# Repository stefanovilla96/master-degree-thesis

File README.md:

# master-degree-thesis
Remote repository about master degree thesis in informatic engineering

# organization of the folders:
    - thesis : contains documentation about the project
    - Winter-v2_firmware : contains firmware for microcontroller for BIA measure with BIA Board & Winter v2
    - EDABoard : contains firmware for microcontroller for EDA Measure
    - EDA Board_Software : contains eclipse project for EDA measure

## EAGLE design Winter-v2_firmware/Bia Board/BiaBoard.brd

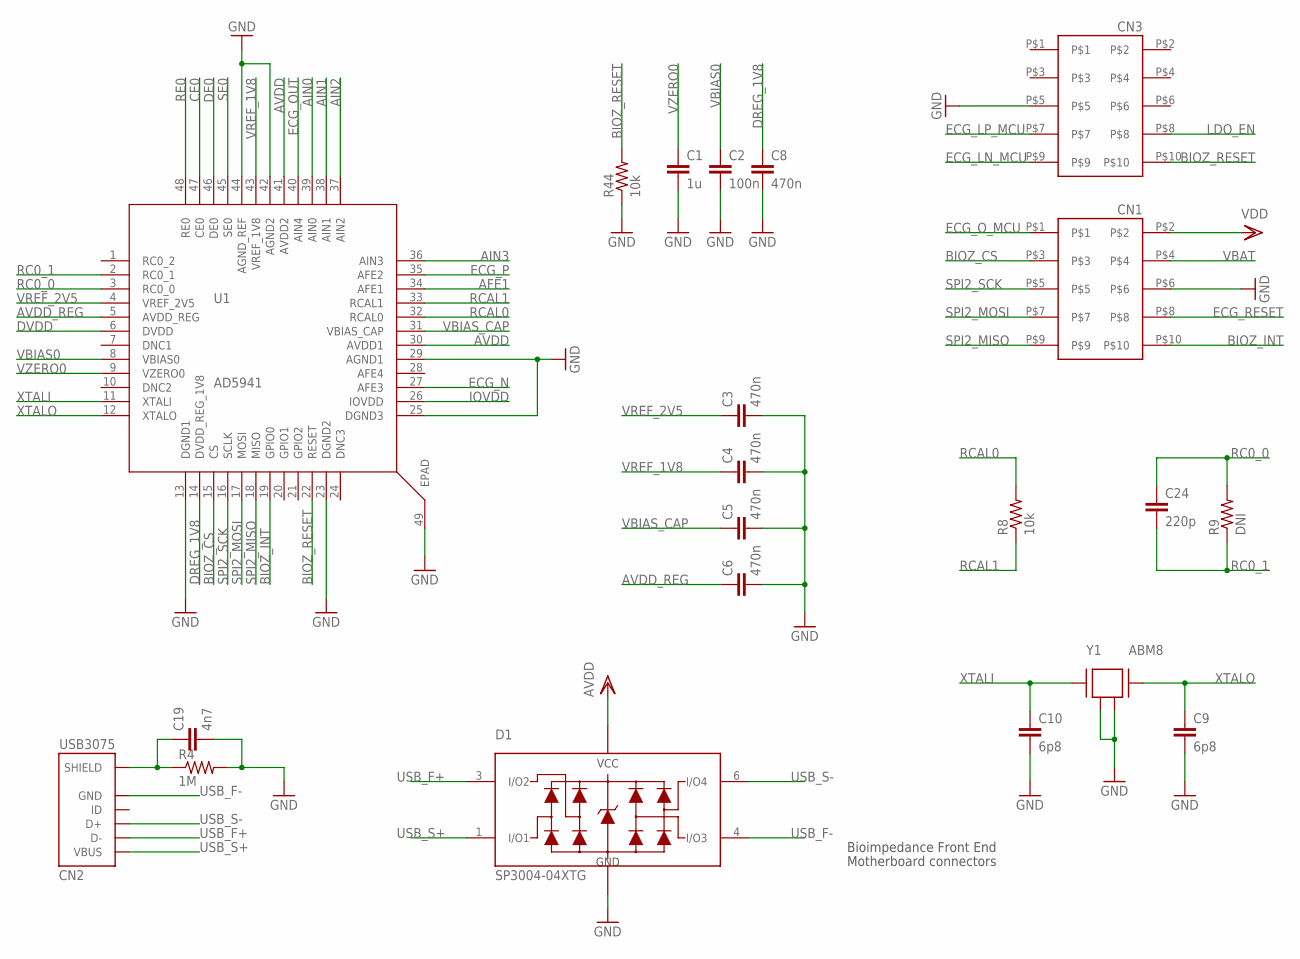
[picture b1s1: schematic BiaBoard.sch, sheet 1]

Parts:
C1: 1u; C0402
C2: 100n; C0402
C3, C4, C5, C6, C8: 470n; C0402
C9, C10: 6p8; C0402
C19: 4n7; C0402
C24: 220p; C0402
CN1, CN3: FTSH-105TO; FTSH-105-D
CN2: USB3075
D1: SP3004-04XTG; SOT50P160X60-6N
R4: 1M; 0402
R8: 10k; 0402; TOLERANCE 0.1%
R9: DNI; 0402
R44: 10k; 0402
U1: AD5941; QFN50P700X700X80-49T510N
Y1: ABM8

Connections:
AFE1: U1.34 (AFE1); also elsewhere on the board
AIN0: U1.39 (AIN0); also elsewhere on the board
AIN1: U1.38 (AIN1); also elsewhere on the board
AIN2: U1.37 (AIN2); also elsewhere on the board
AIN3: U1.36 (AIN3); also elsewhere on the board
AVDD: D1.5 (VCC), U1.30 (AVDD1), U1.41 (AVDD2); also elsewhere on the board
AVDD_REG: C6.P$1 (1), U1.5 (AVDD_REG)
BIOZ_CS: CN1.P$3, U1.15 (CS)
BIOZ_INT: CN1.P$10, U1.19 (GPIO0)
BIOZ_RESET: CN3.P$10, R44.P$2 (2), U1.22 (RESET)
CE0: U1.47 (CE0); also elsewhere on the board
DE0: U1.46 (DE0); also elsewhere on the board
DREG_1V8: C8.P$1 (1), U1.14 (DVDD_REG_1V8)
DVDD: U1.6 (DVDD); also elsewhere on the board
ECG_LN_MCU: CN3.P$9; also elsewhere on the board
ECG_LP_MCU: CN3.P$7; also elsewhere on the board
ECG_N: U1.27 (AFE3); also elsewhere on the board
ECG_OUT: U1.40 (AIN4); also elsewhere on the board
ECG_O_MCU: CN1.P$1; also elsewhere on the board
ECG_P: U1.35 (AFE2); also elsewhere on the board
ECG_RESET: CN1.P$8; also elsewhere on the board
GND: C1.P$2 (2), C2.P$2 (2), C3.P$2 (2), C4.P$2 (2), C5.P$2 (2), C6.P$2 (2), C8.P$2 (2), C9.P$2 (2), C10.P$2 (2), C19.P$2 (2), CN1.P$6, CN3.P$5, D1.2 (GND), R4.P$2 (2), R44.P$1 (1), U1.13 (DGND1), U1.23 (DGND2), U1.25 (DGND3), U1.29 (AGND1), U1.42 (AGND2), U1.44 (AGND_REF), U1.49 (EPAD), Y1.P$2 (2), Y1.P$4 (4); also elsewhere on the board
IOVDD: U1.26 (IOVDD); also elsewhere on the board
LDO_EN: CN3.P$8; also elsewhere on the board
unnamed: C19.P$1 (1), CN2.G1 (SHIELD), CN2.G2 (SHIELD), CN2.G3 (SHIELD), CN2.G4 (SHIELD), CN2.G5 (SHIELD), CN2.G6 (SHIELD), R4.P$1 (1)
RC0_0: C24.P$1 (1), R9.P$2 (2), U1.3 (RC0_0)
RC0_1: C24.P$2 (2), R9.P$1 (1), U1.2 (RC0_1)
RCAL0: R8.P$2 (2), U1.32 (RCAL0)
RCAL1: R8.P$1 (1), U1.33 (RCAL1)
RE0: U1.48 (RE0); also elsewhere on the board
SE0: U1.45 (SE0); also elsewhere on the board
SPI2_MISO: CN1.P$9, U1.18 (MISO)
SPI2_MOSI: CN1.P$7, U1.17 (MOSI)
SPI2_SCK: CN1.P$5, U1.16 (SCLK)
USB_F+: CN2.P2 (D-), D1.3 (I/O2); also elsewhere on the board
USB_F-: CN2.P5 (GND), D1.4 (I/O3); also elsewhere on the board
USB_S+: CN2.P1 (VBUS), D1.1 (I/O1); also elsewhere on the board
USB_S-: CN2.P3 (D+), D1.6 (I/O4); also elsewhere on the board
VBAT: CN1.P$4; also elsewhere on the board
VBIAS0: C2.P$1 (1), U1.8 (VBIAS0)
VBIAS_CAP: C5.P$1 (1), U1.31 (VBIAS_CAP)
VDD: CN1.P$2; also elsewhere on the board
VREF_1V8: C4.P$1 (1), U1.43 (VREF_1V8)
VREF_2V5: C3.P$1 (1), U1.4 (VREF_2V5)
VZERO0: C1.P$1 (1), U1.9 (VZERO0)
XTALI: C10.P$1 (1), U1.11 (XTALI), Y1.P$1 (1)
XTALO: C9.P$1 (1), U1.12 (XTALO), Y1.P$3 (3)

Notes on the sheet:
Bioimpedance Front End
Motherboard connectors

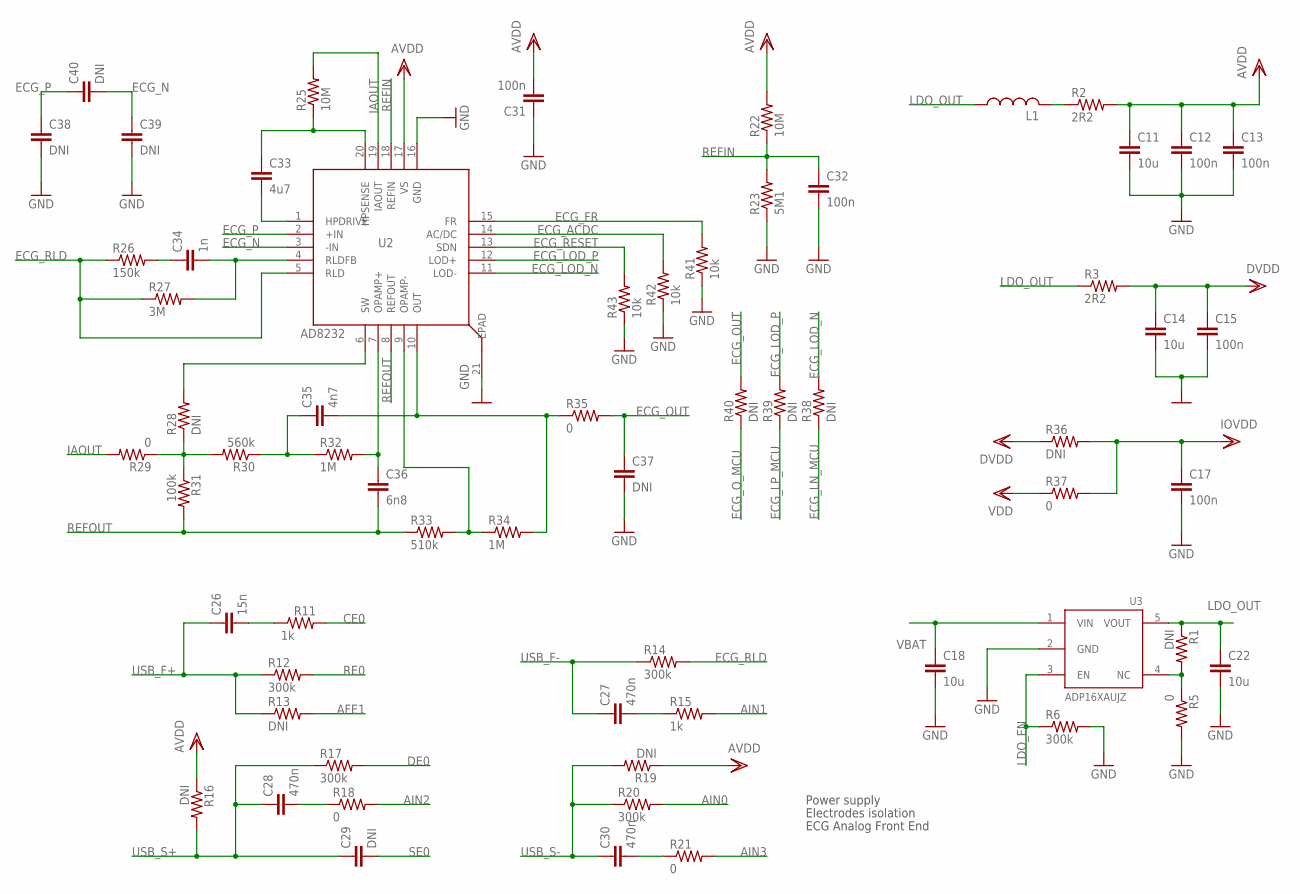
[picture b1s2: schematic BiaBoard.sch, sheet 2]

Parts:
C11, C14, C18, C22: 10u; C0603
C12, C13, C15, C17, C31, C32: 100n; C0402
C26: 15n; C0402
C27, C28, C30: 470n; C0402
C29, C38, C39, C40: DNI; C0402
C33: 4u7; C0402
C34: 1n; C0402
C35: 4n7; C0402
C36: 6n8; C0402
C37: DNI; C0603
L1: L0603; 0603
R1, R13, R16, R19, R28, R36, R38, R39, R40: DNI; 0402
R2, R3: 2R2; 0805
R5, R18, R21, R29, R35, R37: 0; 0402
R6, R12, R14, R17, R20: 300k; 0402
R11, R15: 1k; 0402
R22, R25: 10M; 0402
R23: 5M1; 0402
R26: 150k; 0402
R27: 3M; 0402
R30: 560k; 0402
R31: 100k; 0603
R32, R34: 1M; 0402
R33: 510k; 0402
R41, R42, R43: 10k; 0402
U2: AD8232; QFN50P400X400X75-21T260N
U3: ADP16XAUJZ; TSOT23-5L

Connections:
AFE1: R13.P$2 (2); also elsewhere on the board
AIN0: R20.P$2 (2); also elsewhere on the board
AIN1: R15.P$2 (2); also elsewhere on the board
AIN2: R18.P$2 (2); also elsewhere on the board
AIN3: R21.P$2 (2); also elsewhere on the board
AVDD: C11.P$1 (1), C12.P$1 (1), C13.P$1 (1), C31.P$2 (2), R2.P$2 (2), R16.P$1 (1), R19.P$1 (1), R22.P$2 (2), U2.17 (VS); also elsewhere on the board
CE0: R11.P$2 (2); also elsewhere on the board
DE0: R17.P$2 (2); also elsewhere on the board
DVDD: C14.P$1 (1), C15.P$1 (1), R3.P$2 (2), R36.P$1 (1); also elsewhere on the board
ECG_ACDC: R42.P$2 (2), U2.14 (AC/DC)
ECG_FR: R41.P$2 (2), U2.15 (FR)
ECG_LN_MCU: R38.P$1 (1); also elsewhere on the board
ECG_LOD_N: R38.P$2 (2), U2.11 (LOD-)
ECG_LOD_P: R39.P$2 (2), U2.12 (LOD+)
ECG_LP_MCU: R39.P$1 (1); also elsewhere on the board
ECG_N: C39.P$1 (1), C40.P$2 (2), U2.3 (-IN); also elsewhere on the board
ECG_OUT: C37.P$1 (1), R35.P$2 (2), R40.P$2 (2); also elsewhere on the board
ECG_O_MCU: R40.P$1 (1); also elsewhere on the board
ECG_P: C38.P$1 (1), C40.P$1 (1), U2.2 (+IN); also elsewhere on the board
ECG_RESET: R43.P$2 (2), U2.13 (SDN); also elsewhere on the board
ECG_RLD: R14.P$2 (2), R26.P$1 (1), R27.P$1 (1), U2.5 (RLD)
GND: C11.P$2 (2), C12.P$2 (2), C13.P$2 (2), C14.P$2 (2), C15.P$2 (2), C17.P$2 (2), C18.P$2 (2), C22.P$2 (2), C31.P$1 (1), C32.P$2 (2), C37.P$2 (2), C38.P$2 (2), C39.P$2 (2), R5.P$2 (2), R6.P$2 (2), R23.P$1 (1), R41.P$1 (1), R42.P$1 (1), R43.P$1 (1), U2.16 (GND), U2.21 (EPAD), U3.2 (GND); also elsewhere on the board
IAOUT: R25.P$2 (2), R29.P$2 (2), U2.19 (IAOUT)
IOVDD: C17.P$1 (1), R36.P$2 (2), R37.P$2 (2); also elsewhere on the board
LDO_EN: R6.P$1 (1), U3.3 (EN); also elsewhere on the board
LDO_OUT: C22.P$1 (1), L1.P$1 (1), R1.P$1 (1), R3.P$1 (1), U3.5 (VOUT)
unnamed: L1.P$2 (2), R2.P$1 (1)
unnamed: C26.P$2 (2), R11.P$1 (1)
unnamed: R1.P$2 (2), R5.P$1 (1), U3.4 (NC)
unnamed: C27.P$2 (2), R15.P$1 (1)
unnamed: C30.P$2 (2), R21.P$1 (1)
unnamed: C28.P$2 (2), R18.P$1 (1)
unnamed: C33.P$1 (1), R25.P$1 (1), U2.20 (HPSENSE)
unnamed: C34.P$2 (2), R27.P$2 (2), U2.4 (RLDFB)
unnamed: C33.P$2 (2), U2.1 (HPDRIVE)
unnamed: R28.P$1 (1), R29.P$1 (1), R30.P$2 (2), R31.P$1 (1)
unnamed: C34.P$1 (1), R26.P$2 (2)
unnamed: R28.P$2 (2), U2.6 (SW)
unnamed: C35.P$1 (1), R30.P$1 (1), R32.P$1 (1)
unnamed: C35.P$2 (2), R34.P$2 (2), R35.P$1 (1), U2.10 (OUT)
unnamed: C36.P$1 (1), R32.P$2 (2), U2.7 (OPAMP+)
unnamed: R33.P$2 (2), R34.P$1 (1), U2.9 (OPAMP-)
RE0: R12.P$2 (2); also elsewhere on the board
REFIN: C32.P$1 (1), R22.P$1 (1), R23.P$2 (2), U2.18 (REFIN)
REFOUT: C36.P$2 (2), R31.P$2 (2), R33.P$1 (1), U2.8 (REFOUT)
SE0: C29.P$2 (2); also elsewhere on the board
USB_F+: C26.P$1 (1), R12.P$1 (1), R13.P$1 (1); also elsewhere on the board
USB_F-: C27.P$1 (1), R14.P$1 (1); also elsewhere on the board
USB_S+: C28.P$1 (1), C29.P$1 (1), R16.P$2 (2), R17.P$1 (1); also elsewhere on the board
USB_S-: C30.P$1 (1), R19.P$2 (2), R20.P$1 (1); also elsewhere on the board
VBAT: C18.P$1 (1), U3.1 (VIN); also elsewhere on the board
VDD: R37.P$1 (1); also elsewhere on the board

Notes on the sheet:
Power supply
ECG Analog Front End
Electrodes isolation

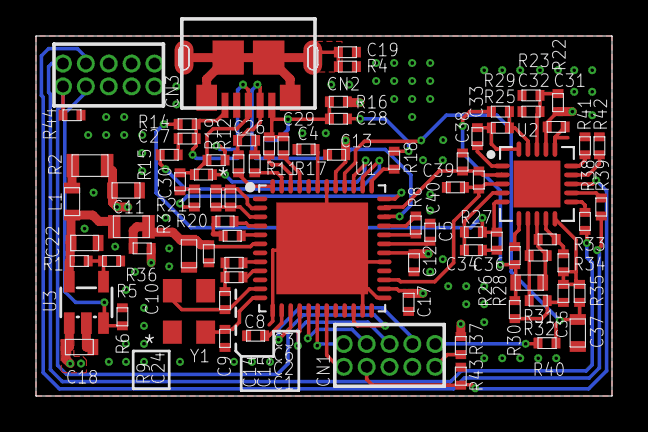
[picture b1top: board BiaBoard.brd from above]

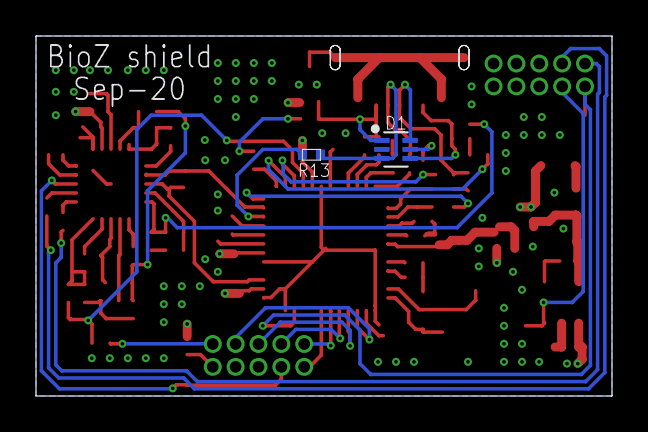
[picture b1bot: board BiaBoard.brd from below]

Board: 4 copper layers, 32.0 x 20.0 mm, 84 parts (2 on the bottom side), 72 nets.

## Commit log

2020-12-18 Compile README.md
2020-12-18 Upload all files
2020-12-18 Added schematic
